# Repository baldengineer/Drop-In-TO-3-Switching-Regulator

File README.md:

## Drop-In TO-3 Switching Regulator
KiCad design files for LM323 Linear regulator replacement for 5 volt applications. Created using KiCad 5.x.

Replaces the 5 volt output, LM323 linear regulator available in a TO-3 package. This regulator was found in the first revision of the Commodore VIC-20. The switching regulator generates significantly less heat than the original linear supply.

Based on a TI [https://www.ti.com/store/ti/en/p/product/?p=TPS563240DDCR](TPS563240DDCR). Capable of supplying up to 3 Amps at 5 volts. 

At 3 amps output, the output ripple is less than 50 mVpp. (Less than 30 mVpp when measurement is band-limited to 20 MHz!)

## Input
Input voltage was only tested with about 9 volts, from the VIC-20's rectified AC input. According to its datasheet, it can operate up to 17 volt in. However, watch the voltage rating of the input capacitors. 

## Output
The TPS563240 has an adjustable output. This design used fixed resistors for a fixed 5.0 volt output. 

## Ground
Ground is connected with the plated-through holes.

## Heat Sink
There are no provisions for direct metal contact to heat-sink the board. With 9 volt in, 3 Amp out, and open air in an ambient of 22C, the hottest component was the inductor at 55C. 

At 1.5 amps or less, the heat rise for the total board is about 5C.

## Bald Engineer on Twitch
This board was designed, built, and tested live with the Bald Engineer. Check out his electronics live stream at: [https://twitch.tv/baldengineer](https://twitch.tv/baldengineer).

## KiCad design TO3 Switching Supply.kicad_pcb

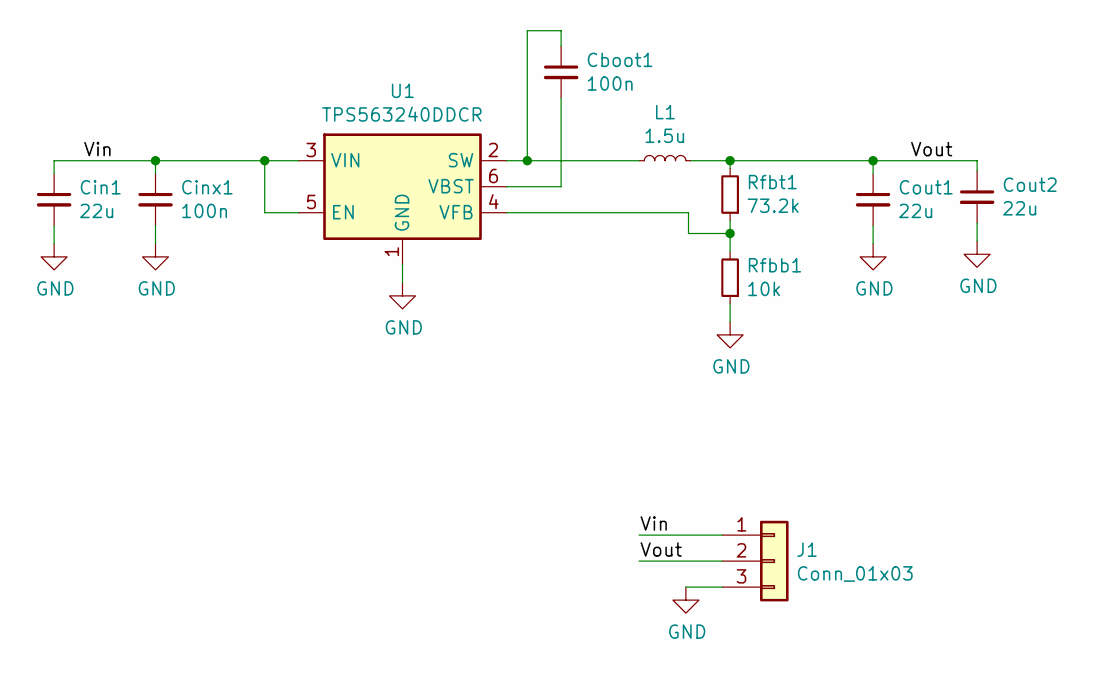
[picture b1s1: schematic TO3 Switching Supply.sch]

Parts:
Cboot1: 100n; C_0805_2012Metric
Cin1: 22u; C_0805_2012Metric
Cinx1: 100n; C_0805_2012Metric
Cout1, Cout2: 22u; C_0805_2012Metric
J1: Conn_01x03; TO-3-withEdgeCuts
L1: 1.5u; L_Bourns_SRP5030T
Rfbb1: 10k; R_0805_2012Metric
Rfbt1: 73.2k; R_0603_1608Metric
U1: TPS563240DDCR; SOT-23-6

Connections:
/Vin: Cin1.1, Cinx1.1, J1.1, U1.3 (VIN), U1.5 (EN)
/Vout: Cout1.1, Cout2.1, J1.2, L1.2, Rfbt1.2
GND: Cin1.2, Cinx1.2, Cout1.2, Cout2.2, J1.3, Rfbb1.1, U1.1 (GND)
unnamed: Cboot1.1, L1.1, U1.2 (SW)
unnamed: Cboot1.2, U1.6 (VBST)
unnamed: Rfbb1.2, Rfbt1.1, U1.4 (VFB)

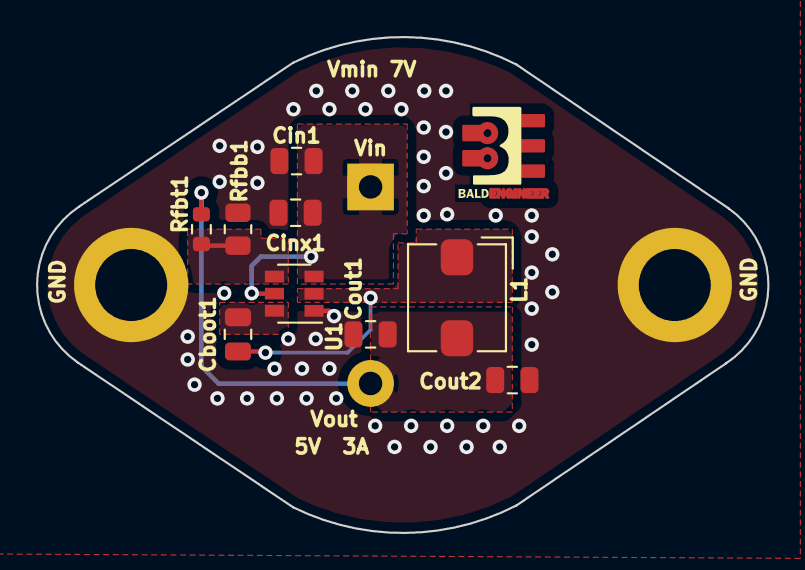
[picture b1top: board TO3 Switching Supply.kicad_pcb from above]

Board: 2 copper layers, 40.6 x 27.5 mm, 11 parts (0 on the bottom side), 6 nets.

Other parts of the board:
svg2mod: G***; BE5

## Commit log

2020-11-08 Initial Commit
    Board tested and working.
